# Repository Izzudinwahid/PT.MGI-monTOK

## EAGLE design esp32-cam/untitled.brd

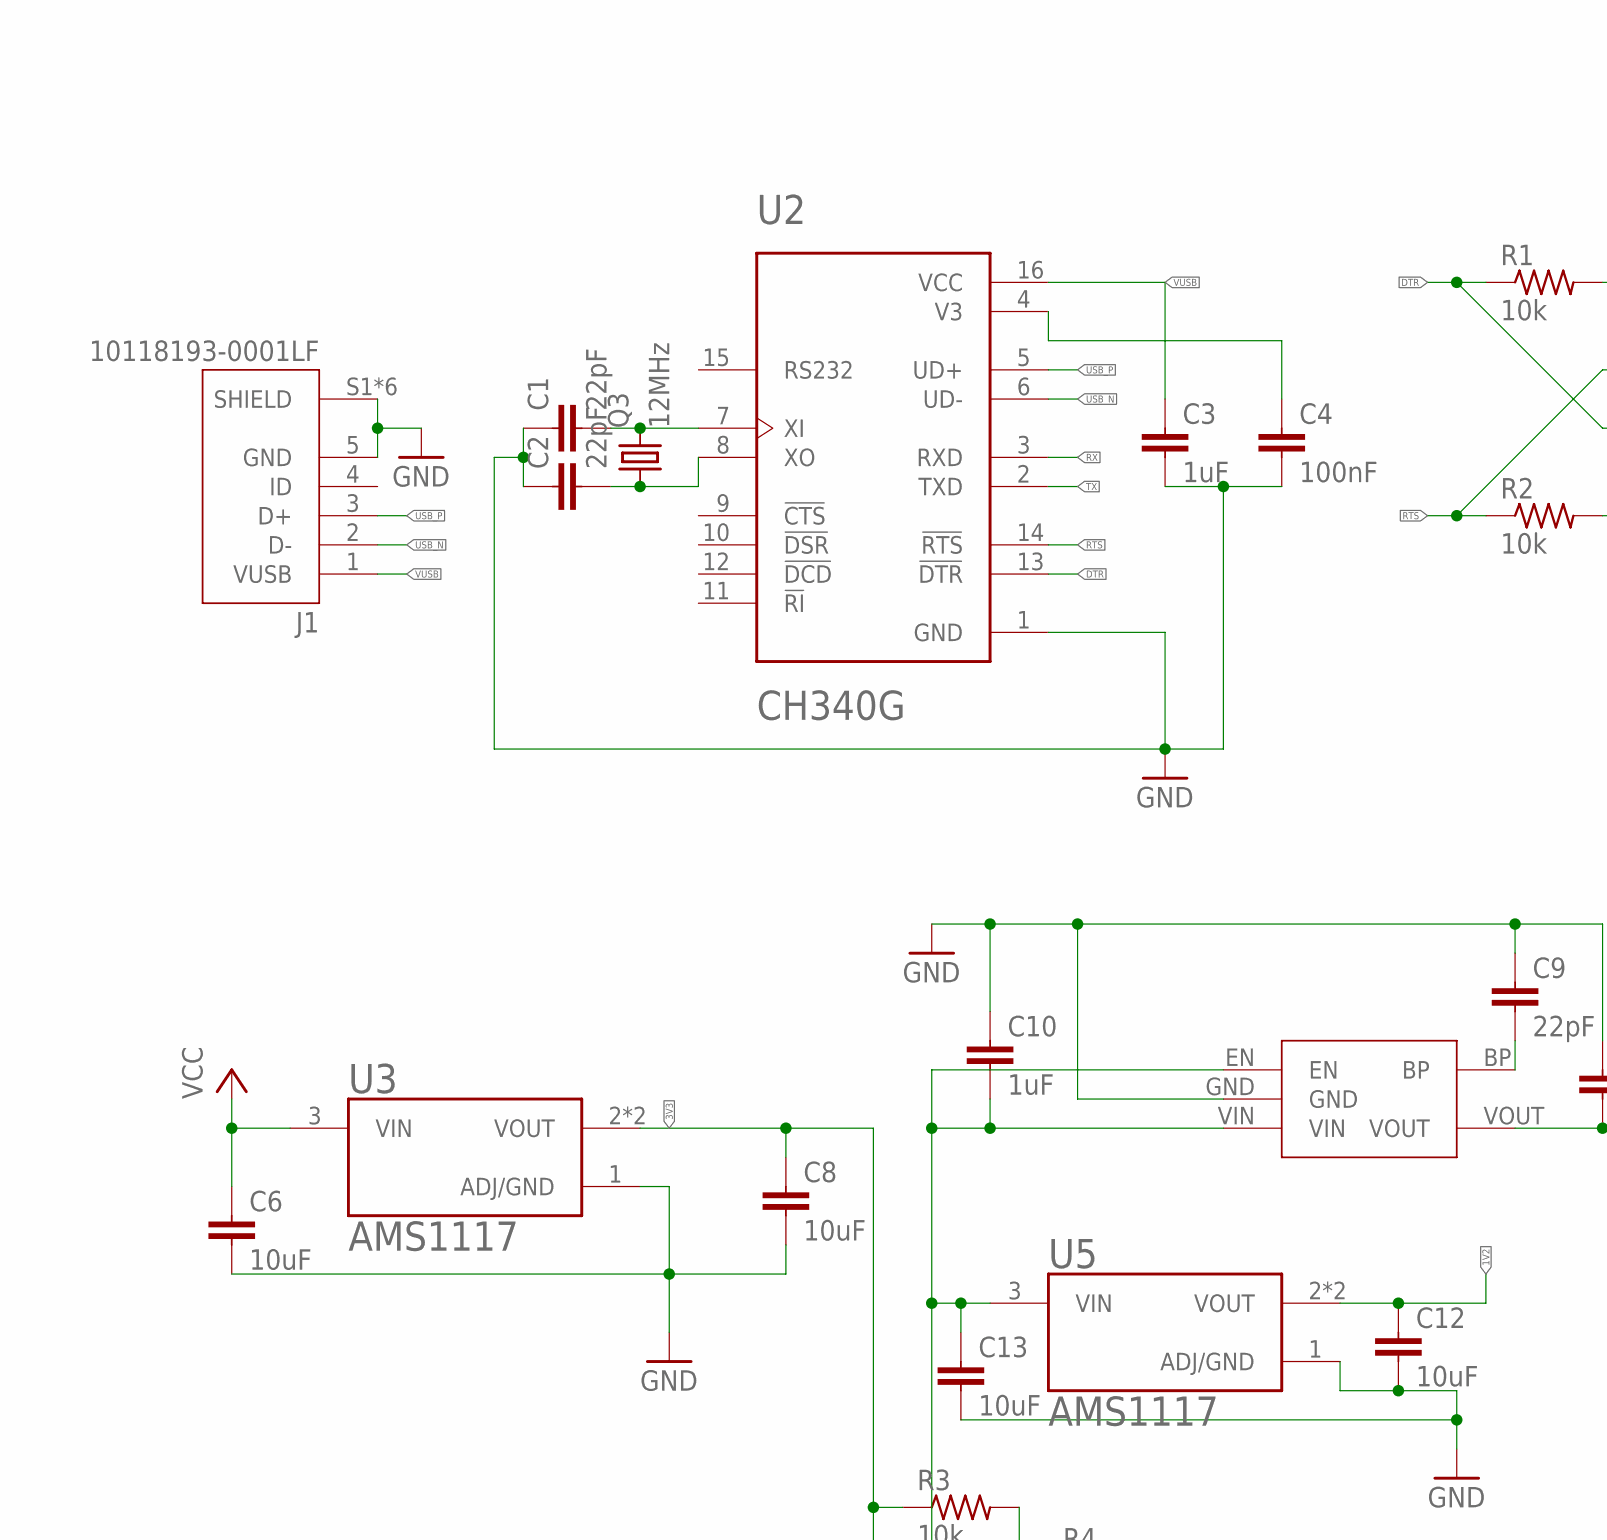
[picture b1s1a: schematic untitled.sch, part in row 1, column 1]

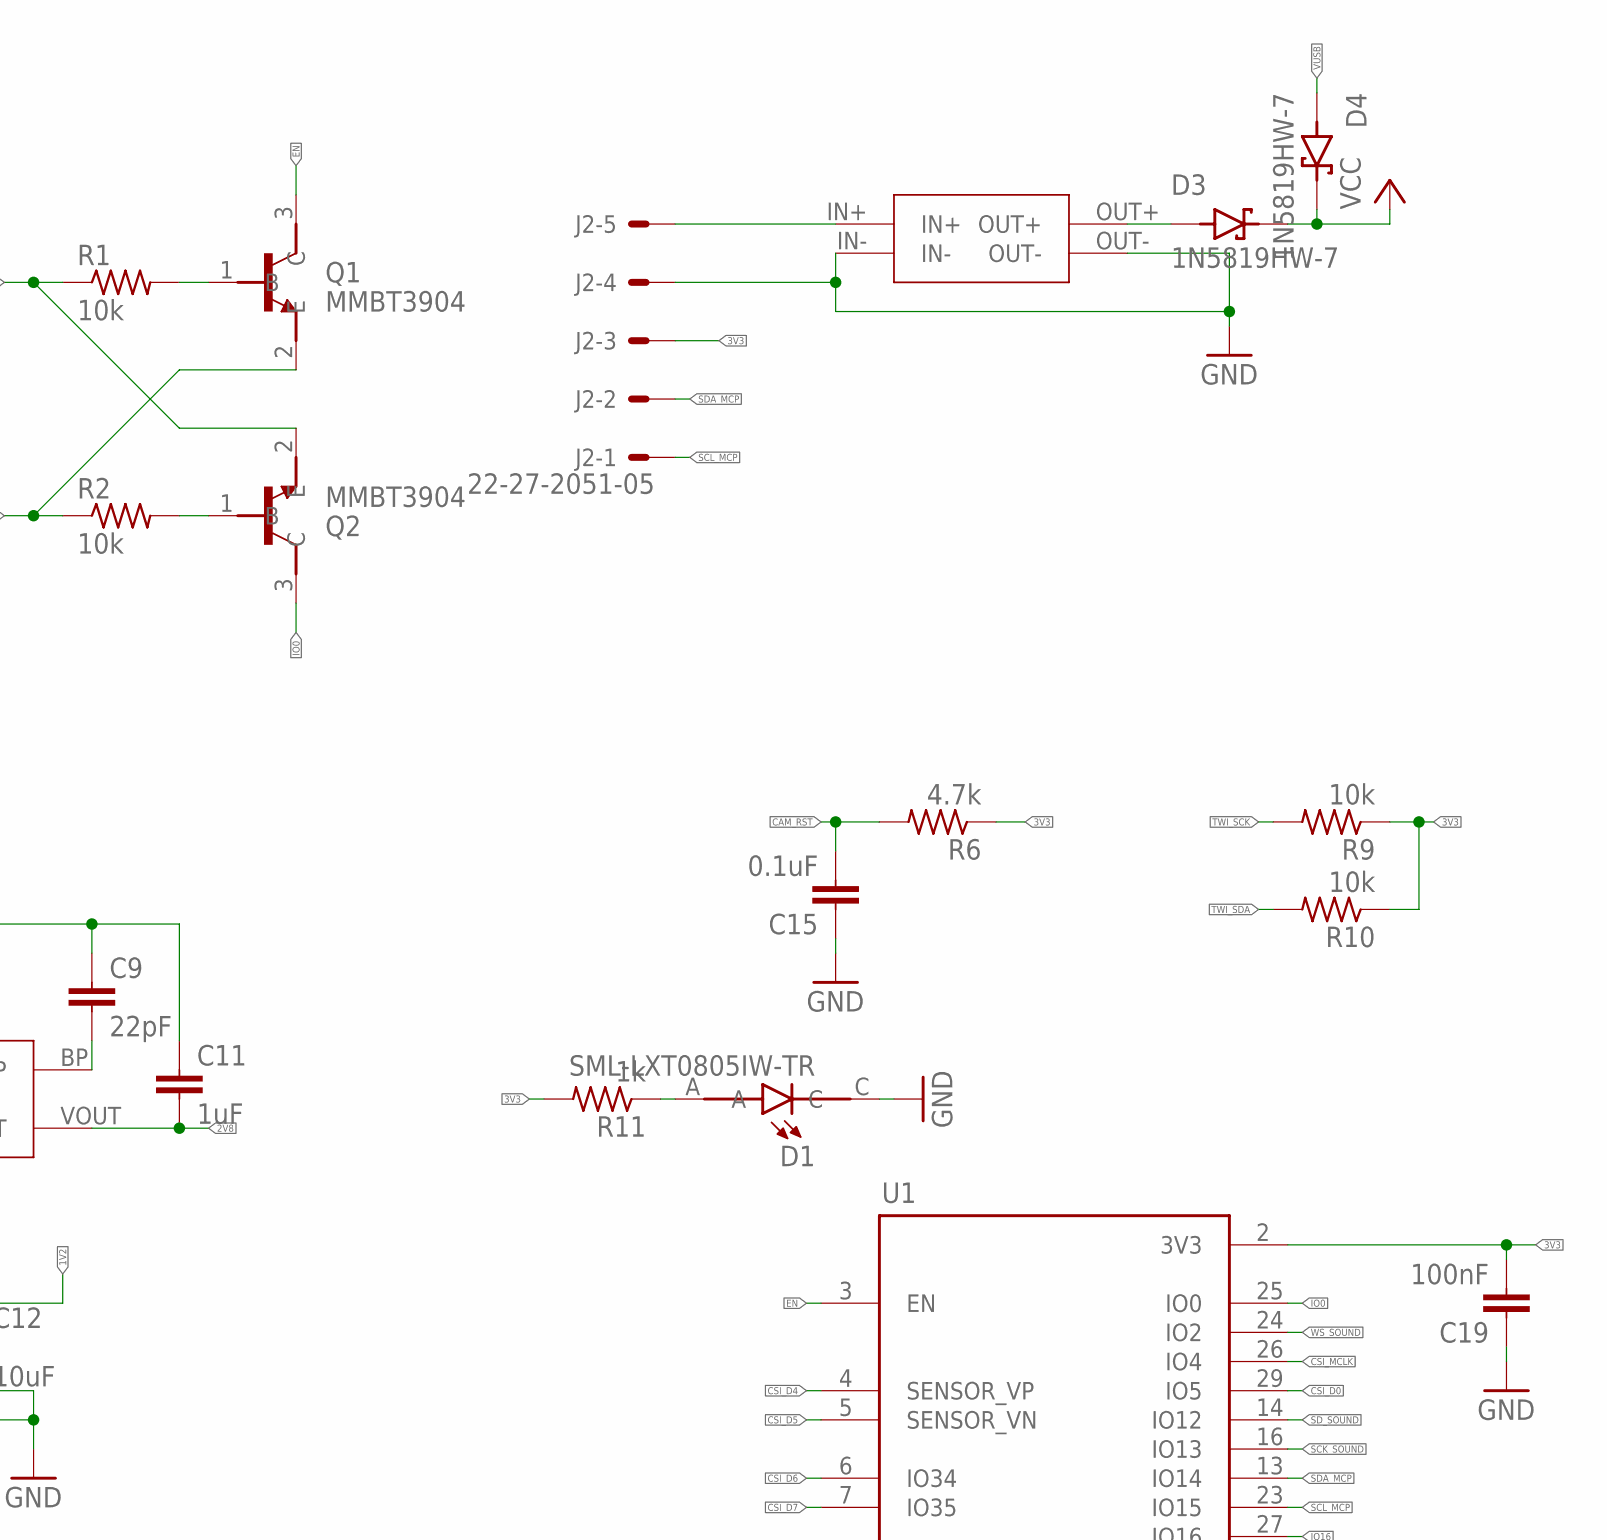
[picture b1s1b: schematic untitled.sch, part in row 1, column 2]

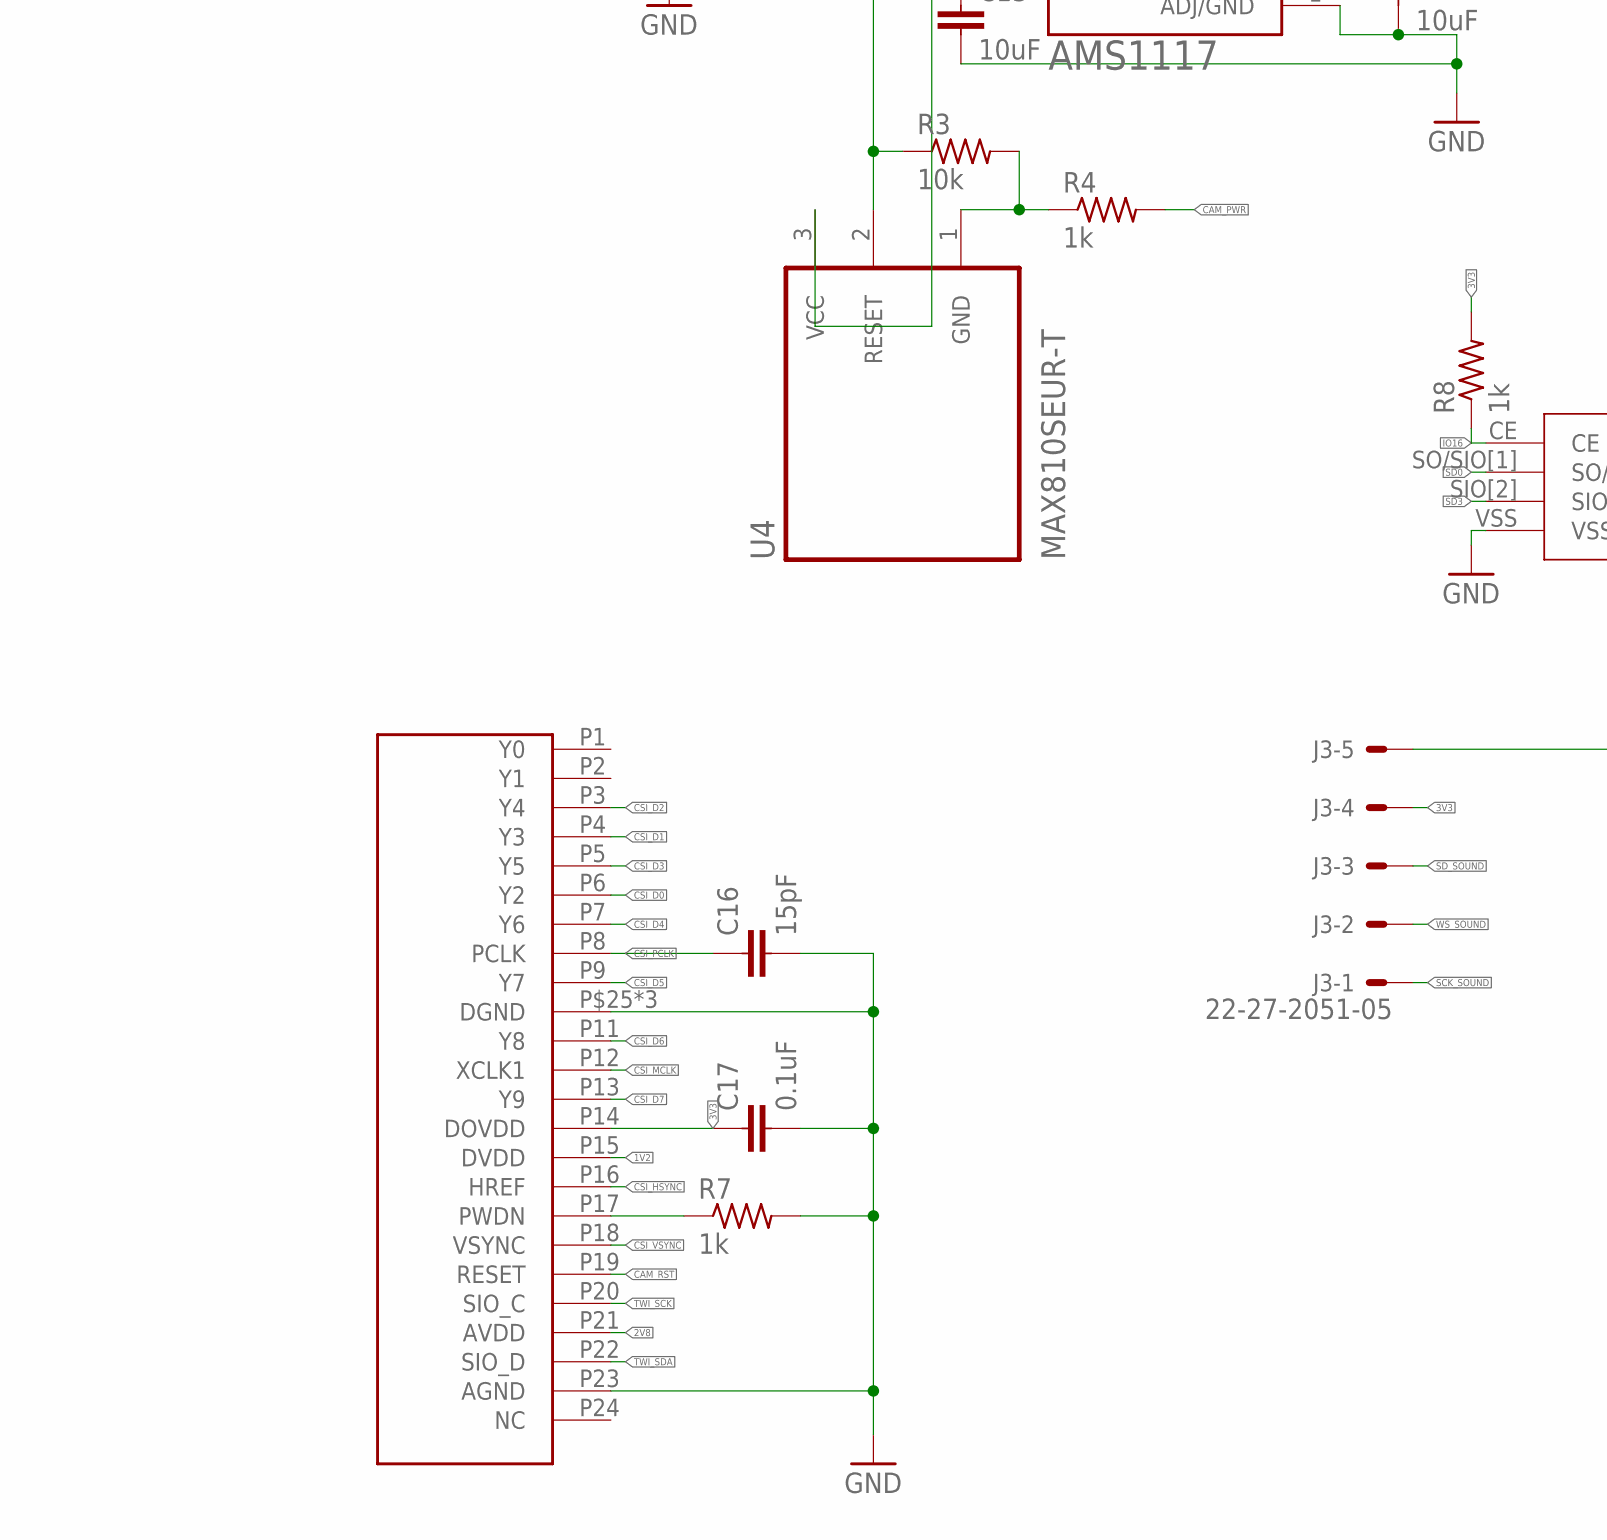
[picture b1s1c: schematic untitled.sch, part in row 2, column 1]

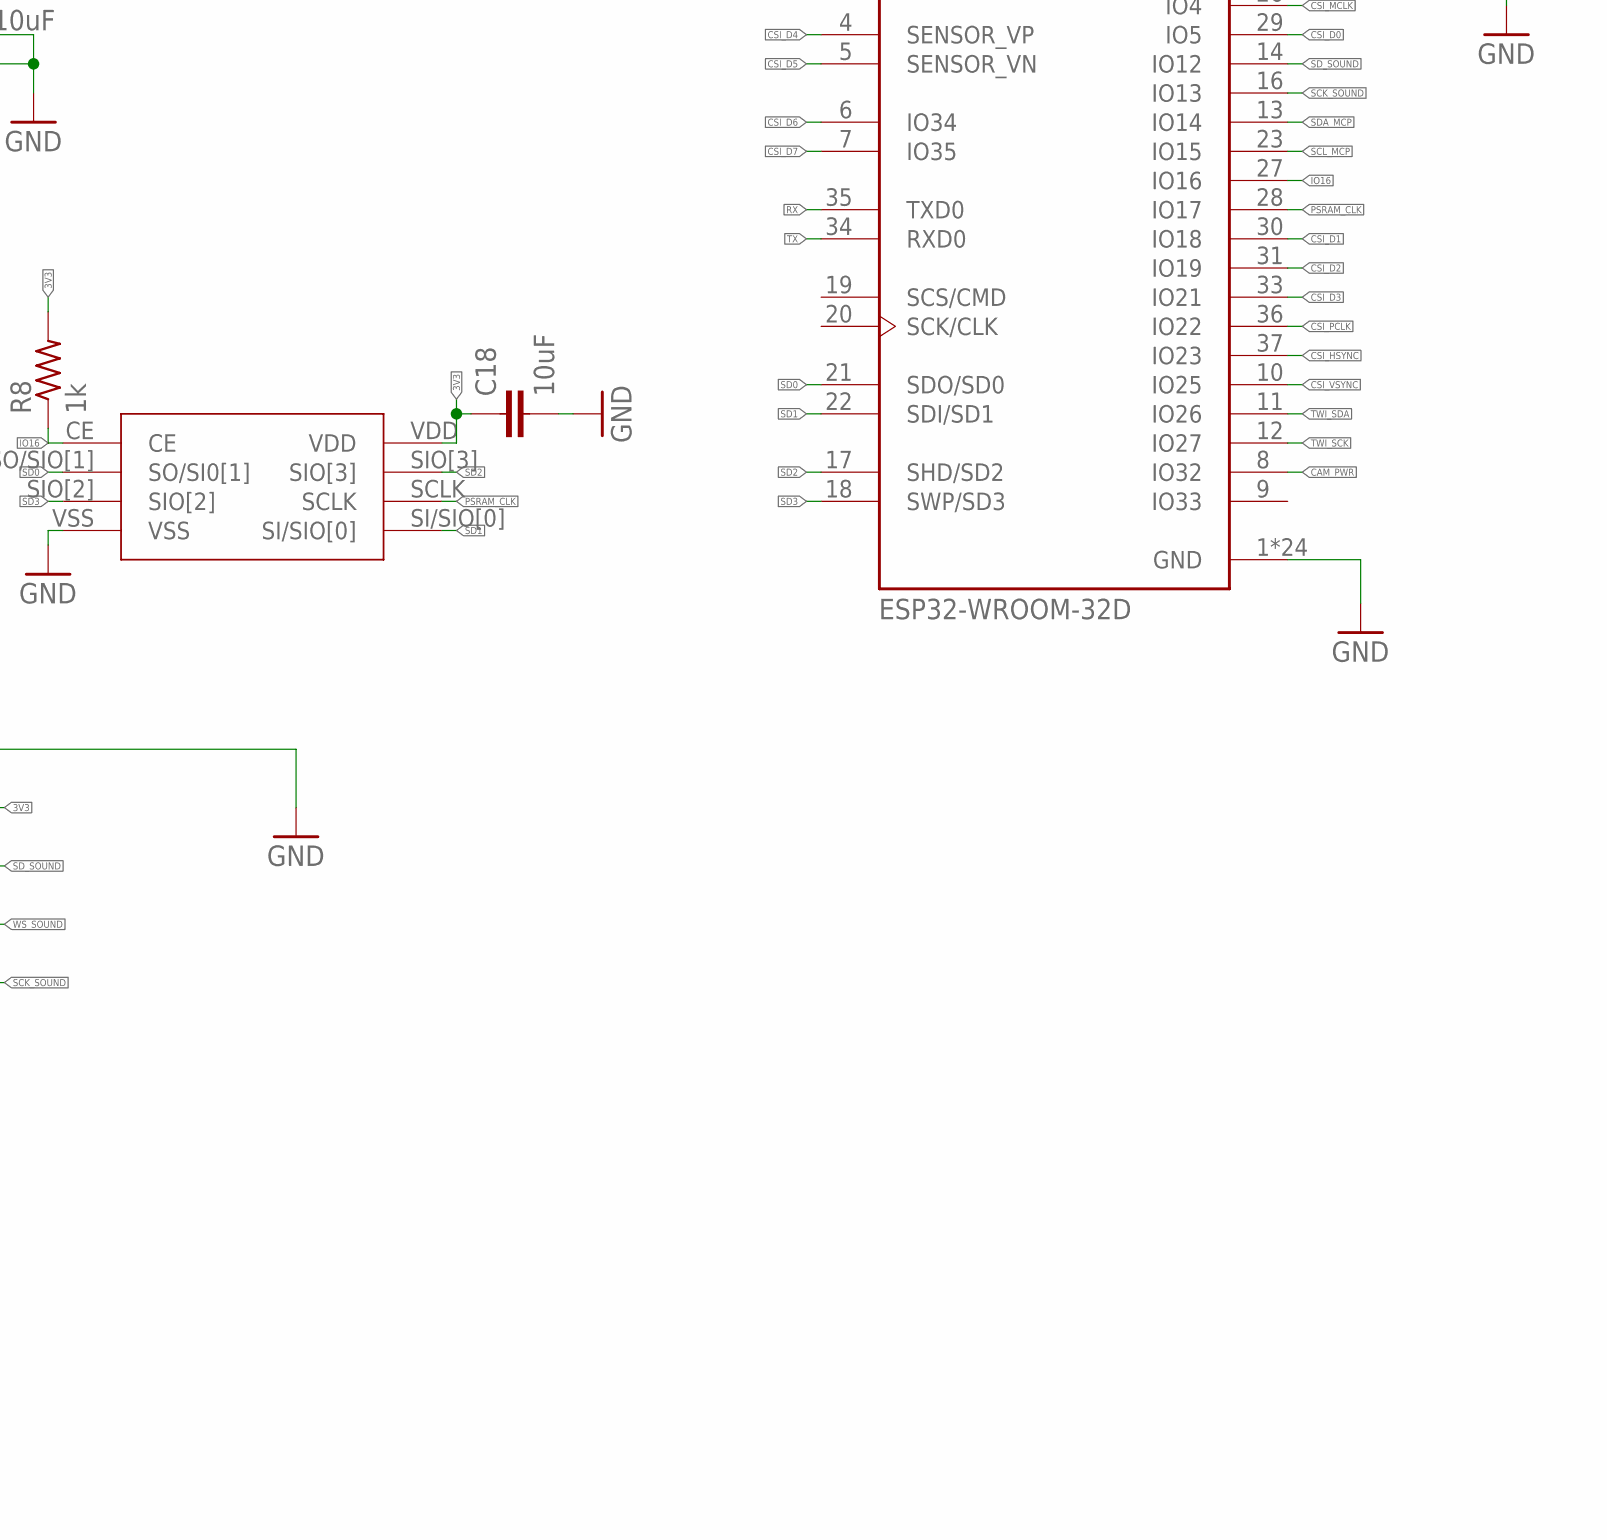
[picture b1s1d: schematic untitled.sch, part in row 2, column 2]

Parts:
APS6404L1: APS6404L
C1, C2, C9: 22pF; C0805K
C3, C10, C11: 1uF; C0805K
C4, C19: 100nF; C0805K
C6, C8, C12, C13, C18: 10uF; C0805K
C15, C17: 0.1uF; C0805K
C16: 15pF; C0805K
CAM1: OV2640; FPC-24
D1: SML-LXT0805IW-TR; LEDC2012X120N
D3, D4: 1N5819HW-7; SOD3715X145N
J1: 10118193-0001LF; FCI_10118193-0001LF
J2, J3: 22-27-2051-05; 6410-05
MINI1: MINI560
Q1, Q2: MMBT3904; SOT95P240X120-3N
Q3: 12MHz; SM49
R1, R2, R3, R9, R10: 10k; M0805
R4, R7, R8, R11: 1k; M0805
R6: 4.7k; M0805
RT9193-28GB1: RT9193-28GB; SOT94P279X129-5N
U1: ESP32-WROOM-32D; MODULE_ESP32-WROOM-32D
U2: CH340G; SOIC127P600X180-16N
U3, U5: AMS1117; SOT229P700X180-4N
U4: MAX810SEUR-T; SOT95P237X112-3N

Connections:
1V2: C12.1, CAM1.P15 (DVDD), U5.2 (VOUT), U5.4 (VOUT)
2V8: C11.2, CAM1.P21 (AVDD), RT9193-28GB1.VOUT
3V3: APS6404L1.VDD, C8.1, C17.1, C18.1, C19.2, CAM1.P14 (DOVDD), J2.3, J3.4, R3.1, R6.1, R8.2, R9.1, R10.1, R11.2, U1.2 (3V3), U3.2 (VOUT), U3.4 (VOUT), U4.2 (RESET)
CAM_PWR: R4.2, U1.8 (IO32)
CAM_RST: C15.2, CAM1.P19 (RESET), R6.2
CSI_D0: CAM1.P6 (Y2), U1.29 (IO5)
CSI_D1: CAM1.P4 (Y3), U1.30 (IO18)
CSI_D2: CAM1.P3 (Y4), U1.31 (IO19)
CSI_D3: CAM1.P5 (Y5), U1.33 (IO21)
CSI_D4: CAM1.P7 (Y6), U1.4 (SENSOR_VP)
CSI_D5: CAM1.P9 (Y7), U1.5 (SENSOR_VN)
CSI_D6: CAM1.P11 (Y8), U1.6 (IO34)
CSI_D7: CAM1.P13 (Y9), U1.7 (IO35)
CSI_HSYNC: CAM1.P16 (HREF), U1.37 (IO23)
CSI_MCLK: CAM1.P12 (XCLK1), U1.26 (IO4)
CSI_PCLK: C16.1, CAM1.P8 (PCLK), U1.36 (IO22)
CSI_VSYNC: CAM1.P18 (VSYNC), U1.10 (IO25)
DTR: Q2.2 (E), R1.1, U2.13 (!DTR)
EN: Q1.3 (C), U1.3 (EN)
GND: APS6404L1.VSS, C1.1, C2.1, C3.2, C4.2, C6.2, C8.2, C9.1, C10.1, C11.1, C12.2, C13.2, C15.1, C16.2, C17.2, C18.2, C19.1, CAM1.P10 (DGND), CAM1.P23 (AGND), CAM1.P$25 (DGND), CAM1.P$26 (DGND), D1.C, J1.5 (GND), J1.S1 (SHIELD), J1.S2 (SHIELD), J1.S3 (SHIELD), J1.S4 (SHIELD), J1.S5 (SHIELD), J1.S6 (SHIELD), J2.4, J3.5, MINI1.IN-, MINI1.OUT-, R7.2, RT9193-28GB1.GND, U1.1 (GND), U1.15 (GND), U1.38 (GND), U1.39_1 (GND), U1.39_2 (GND), U1.39_3 (GND), U1.39_4 (GND), U1.39_5 (GND), U1.39_6 (GND), U1.39_7 (GND), U1.39_8 (GND), U1.39_9 (GND), U1.39_10 (GND), U1.39_11 (GND), U1.39_12 (GND), U1.39_13 (GND), U1.39_14 (GND), U1.39_15 (GND), U1.39_16 (GND), U1.39_17 (GND), U1.39_18 (GND), U1.39_19 (GND), U1.39_20 (GND), U1.39_21 (GND), U2.1 (GND), U3.1 (ADJ/GND), U5.1 (ADJ/GND)
IO0: Q2.3 (C), U1.25 (IO0)
IO16: APS6404L1.CE, R8.1, U1.27 (IO16)
unnamed: C1.2, Q3.2, U2.7 (XI)
unnamed: C2.2, Q3.1, U2.8 (XO)
unnamed: Q1.1 (B), R1.2
unnamed: R3.2, R4.1, U4.1 (GND)
unnamed: D1.A, R11.1
unnamed: J2.5, MINI1.IN+
unnamed: C10.2, C13.1, RT9193-28GB1.EN, RT9193-28GB1.VIN, U4.3 (VCC), U5.3 (VIN)
unnamed: C4.1, U2.4 (V3)
unnamed: Q2.1 (B), R2.2
unnamed: C9.2, RT9193-28GB1.BP
unnamed: D3.A, MINI1.OUT+
unnamed: CAM1.P17 (PWDN), R7.1
PSRAM_CLK: APS6404L1.SCLK, U1.28 (IO17)
RTS: Q1.2 (E), R2.1, U2.14 (!RTS)
RX: U1.35 (TXD0), U2.3 (RXD)
SCK_SOUND: J3.1, U1.16 (IO13)
SCL_MCP: J2.1, U1.23 (IO15)
SD0: APS6404L1.SO/SIO[1] (SO/SI0[1]), U1.21 (SDO/SD0)
SD1: APS6404L1.SI/SIO[0], U1.22 (SDI/SD1)
SD2: APS6404L1.SIO[3], U1.17 (SHD/SD2)
SD3: APS6404L1.SIO[2], U1.18 (SWP/SD3)
SDA_MCP: J2.2, U1.13 (IO14)
SD_SOUND: J3.3, U1.14 (IO12)
TWI_SCK: CAM1.P20 (SIO_C), R9.2, U1.12 (IO27)
TWI_SDA: CAM1.P22 (SIO_D), R10.2, U1.11 (IO26)
TX: U1.34 (RXD0), U2.2 (TXD)
USB_N: J1.2 (D-), U2.6 (UD-)
USB_P: J1.3 (D+), U2.5 (UD+)
VCC: C6.1, D3.C (K), D4.C (K), U3.3 (VIN)
VUSB: C3.1, D4.A, J1.1 (VUSB), U2.16 (VCC)
WS_SOUND: J3.2, U1.24 (IO2)

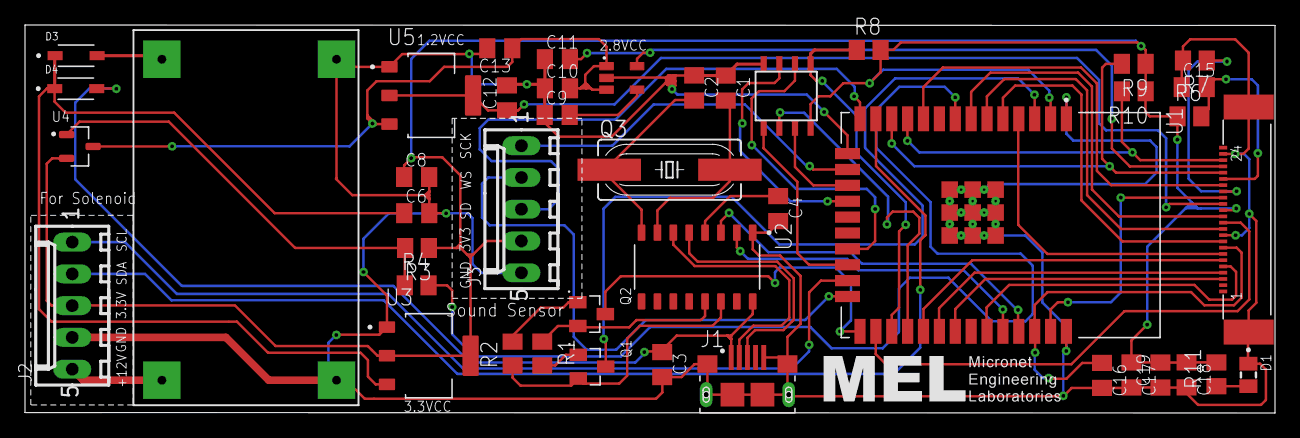
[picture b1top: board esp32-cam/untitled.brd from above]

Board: 2 copper layers, 100.0 x 31.0 mm, 44 parts (0 on the bottom side), 53 nets.

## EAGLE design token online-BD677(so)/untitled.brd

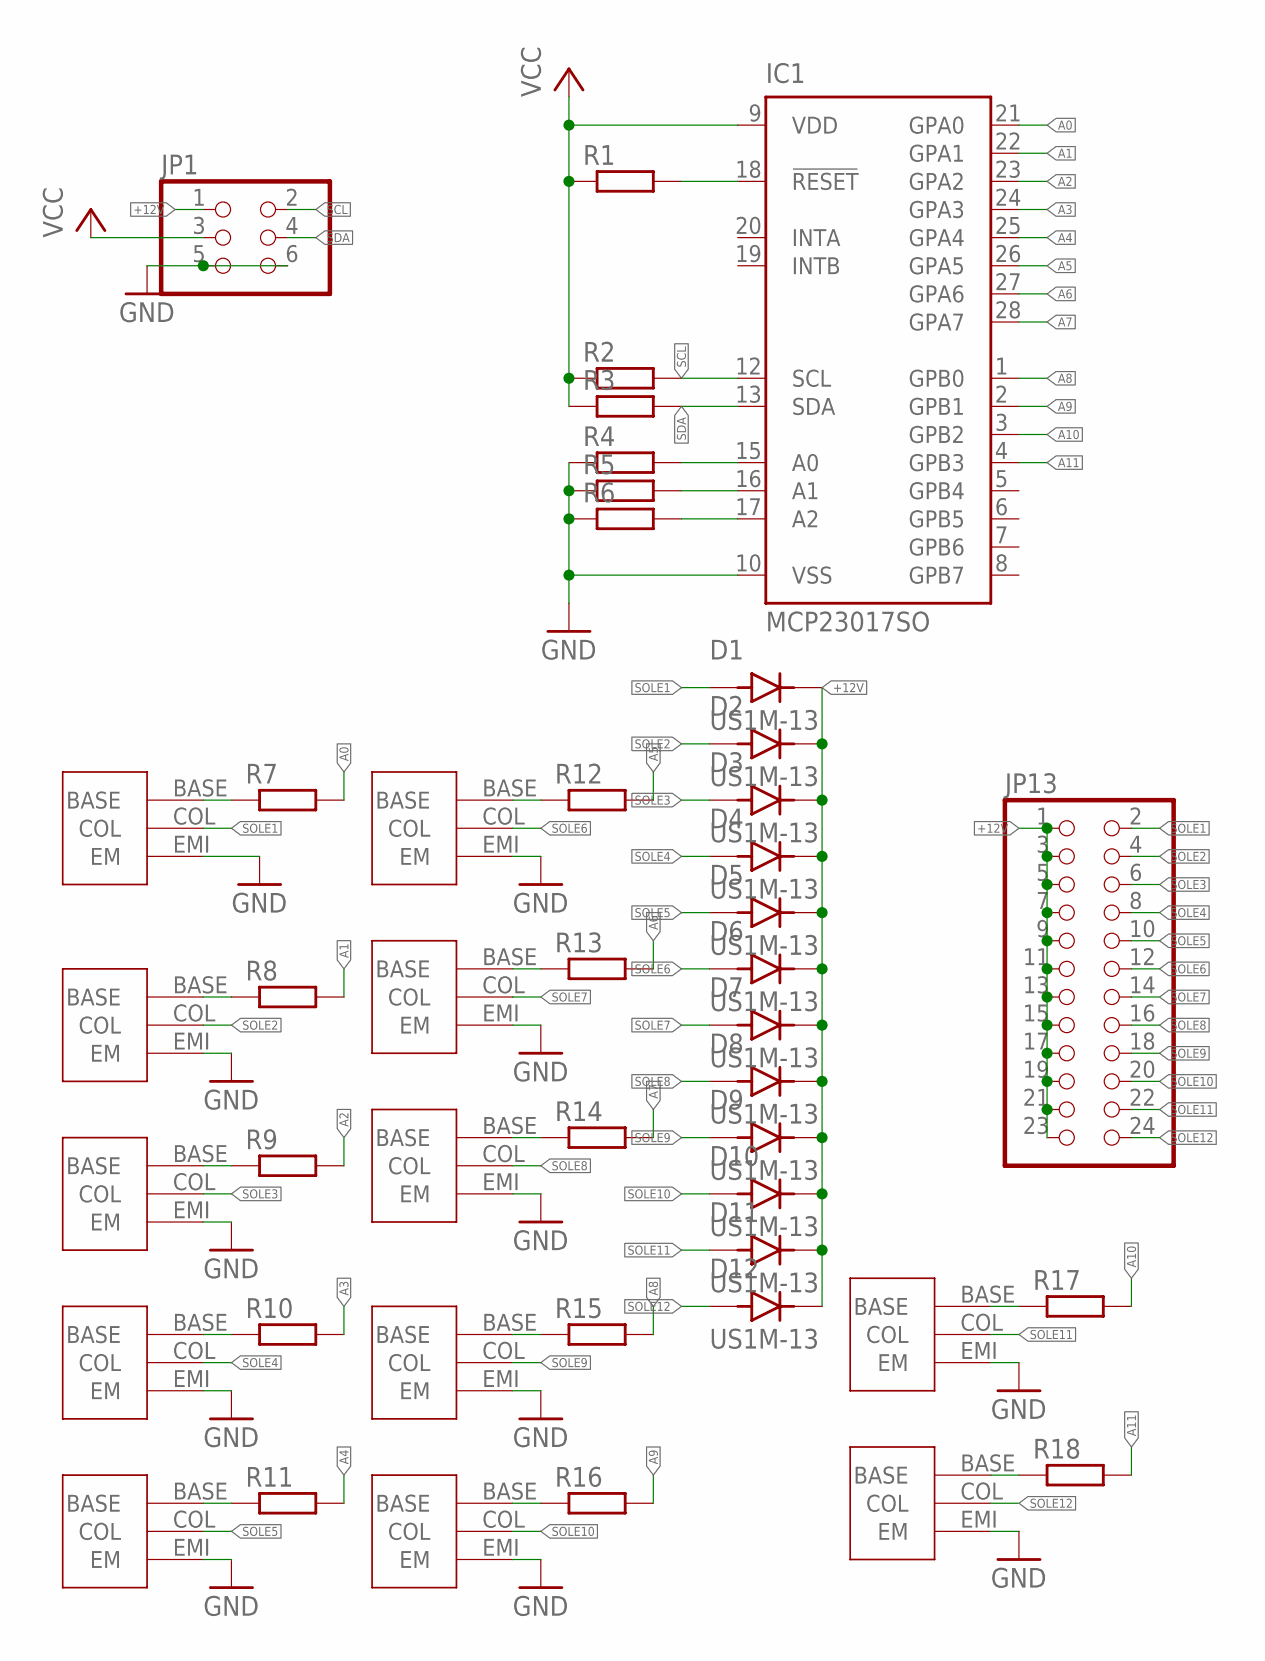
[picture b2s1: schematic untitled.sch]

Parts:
BD677-SMD1, BD677-SMD2, BD677-SMD3, BD677-SMD4, BD677-SMD5, BD677-SMD6, BD677-SMD7, BD677-SMD8, BD677-SMD9, BD677-SMD10, BD677-SMD11, BD677-SMD12: BD677-SMD
D1, D2, D3, D4, D5, D6, D7, D8, D9, D10, D11, D12: US1M-13; DIOM5226X240N
IC1: MCP23017SO; SO28W
JP1: PINHD-2X3; 2X03
JP13: PINHD-2X12; 2X12
R1, R2, R3, R4, R5, R6, R7, R8, R9, R10, R11, R12, R13, R14, R15, R16, R17, R18: R-EU_R0805; R0805

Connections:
+12V: D1.C (K), D2.C (K), D3.C (K), D4.C (K), D5.C (K), D6.C (K), D7.C (K), D8.C (K), D9.C (K), D10.C (K), D11.C (K), D12.C (K), JP1.1, JP13.1, JP13.3, JP13.5, JP13.7, JP13.9, JP13.11, JP13.13, JP13.15, JP13.17, JP13.19, JP13.21, JP13.23
A0: IC1.21 (GPA0), R7.2
A1: IC1.22 (GPA1), R8.2
A2: IC1.23 (GPA2), R9.2
A3: IC1.24 (GPA3), R10.2
A4: IC1.25 (GPA4), R11.2
A5: IC1.26 (GPA5), R12.2
A6: IC1.27 (GPA6), R13.2
A7: IC1.28 (GPA7), R14.2
A8: IC1.1 (GPB0), R15.2
A9: IC1.2 (GPB1), R16.2
A10: IC1.3 (GPB2), R17.2
A11: IC1.4 (GPB3), R18.2
GND: BD677-SMD1.EMI (EM), BD677-SMD2.EMI (EM), BD677-SMD3.EMI (EM), BD677-SMD4.EMI (EM), BD677-SMD5.EMI (EM), BD677-SMD6.EMI (EM), BD677-SMD7.EMI (EM), BD677-SMD8.EMI (EM), BD677-SMD9.EMI (EM), BD677-SMD10.EMI (EM), BD677-SMD11.EMI (EM), BD677-SMD12.EMI (EM), IC1.10 (VSS), JP1.5, JP1.6, R4.1, R5.1, R6.1
unnamed: IC1.18 (!RESET), R1.2
unnamed: BD677-SMD1.BASE, R7.1
unnamed: BD677-SMD2.BASE, R8.1
unnamed: IC1.15 (A0), R4.2
unnamed: IC1.16 (A1), R5.2
unnamed: IC1.17 (A2), R6.2
unnamed: BD677-SMD3.BASE, R9.1
unnamed: BD677-SMD6.BASE, R12.1
unnamed: BD677-SMD7.BASE, R13.1
unnamed: BD677-SMD8.BASE, R14.1
unnamed: BD677-SMD4.BASE, R10.1
unnamed: BD677-SMD5.BASE, R11.1
unnamed: BD677-SMD9.BASE, R15.1
unnamed: BD677-SMD10.BASE, R16.1
unnamed: BD677-SMD11.BASE, R17.1
unnamed: BD677-SMD12.BASE, R18.1
SCL: IC1.12 (SCL), JP1.2, R2.2
SDA: IC1.13 (SDA), JP1.4, R3.2
SOLE1: BD677-SMD1.COL, D1.A, JP13.2
SOLE2: BD677-SMD2.COL, D2.A, JP13.4
SOLE3: BD677-SMD3.COL, D3.A, JP13.6
SOLE4: BD677-SMD4.COL, D4.A, JP13.8
SOLE5: BD677-SMD5.COL, D5.A, JP13.10
SOLE6: BD677-SMD6.COL, D6.A, JP13.12
SOLE7: BD677-SMD7.COL, D7.A, JP13.14
SOLE8: BD677-SMD8.COL, D8.A, JP13.16
SOLE9: BD677-SMD9.COL, D9.A, JP13.18
SOLE10: BD677-SMD10.COL, D10.A, JP13.20
SOLE11: BD677-SMD11.COL, D11.A, JP13.22
SOLE12: BD677-SMD12.COL, D12.A, JP13.24
VCC: IC1.9 (VDD), JP1.3, R1.1, R2.1, R3.1

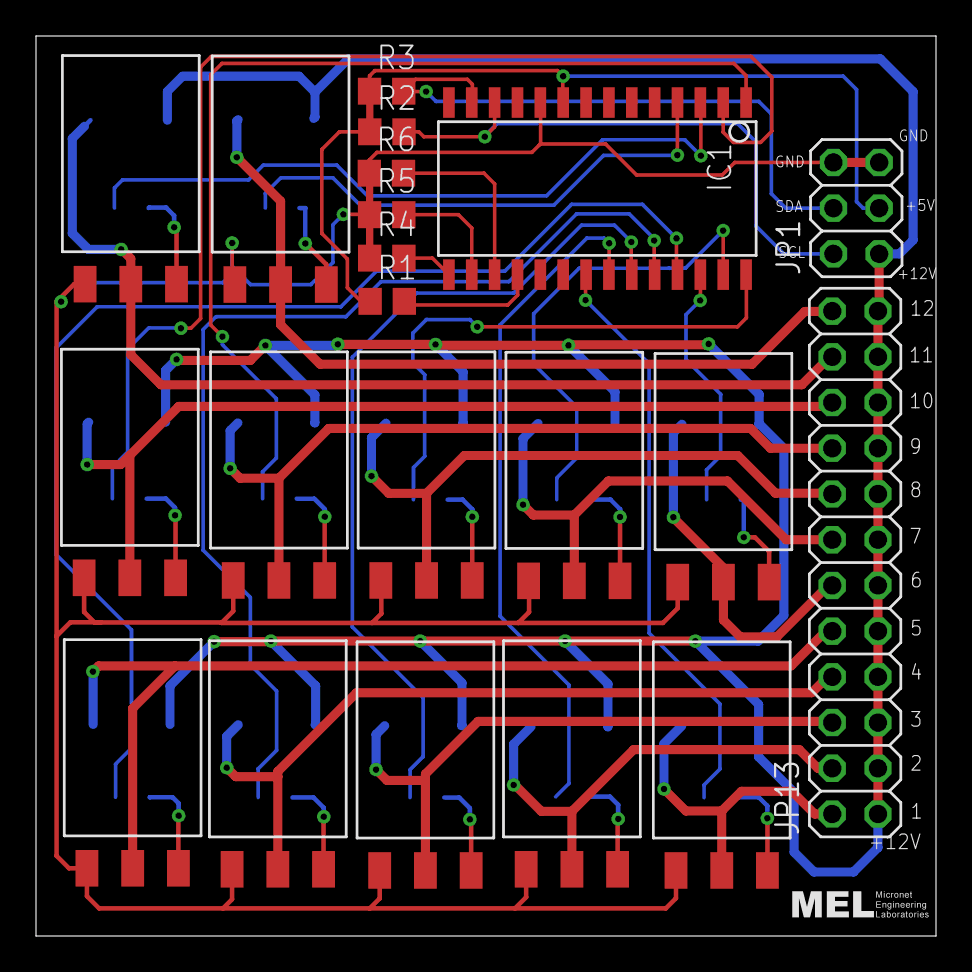
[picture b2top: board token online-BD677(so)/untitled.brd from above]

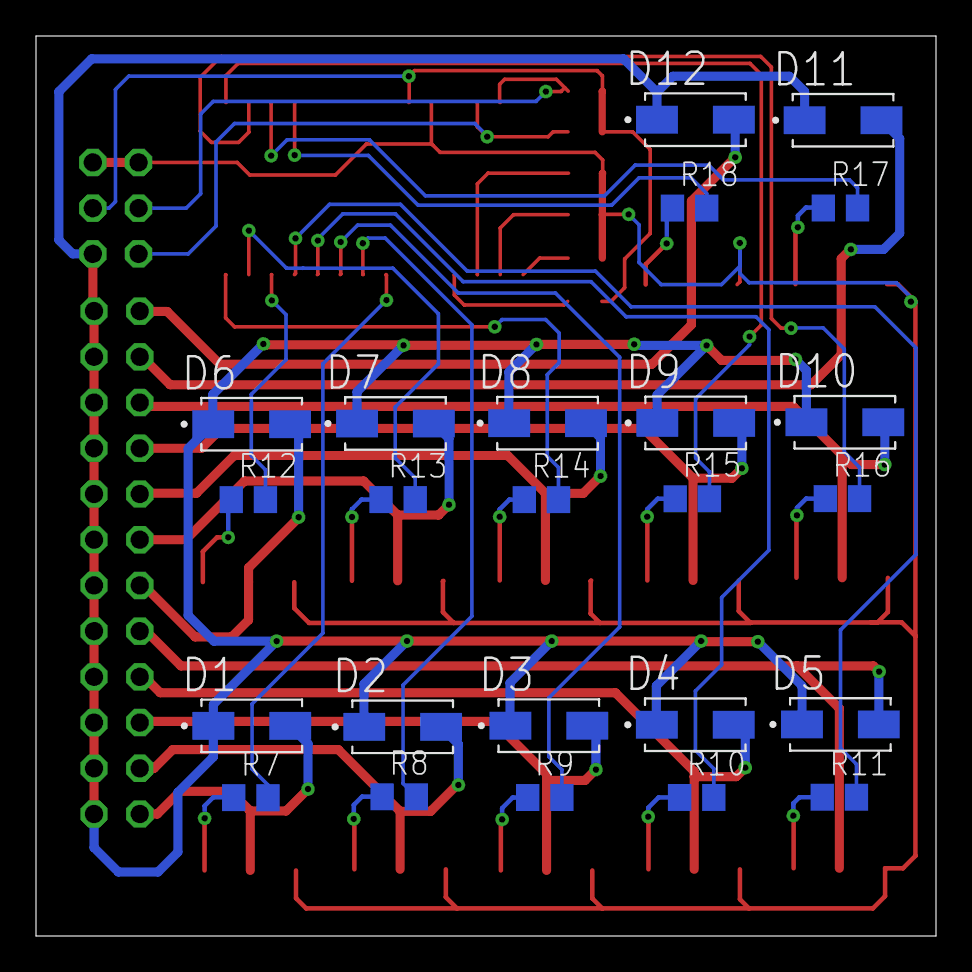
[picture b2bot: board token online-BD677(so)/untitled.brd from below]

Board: 2 copper layers, 50.0 x 50.0 mm, 45 parts (24 on the bottom side), 45 nets.

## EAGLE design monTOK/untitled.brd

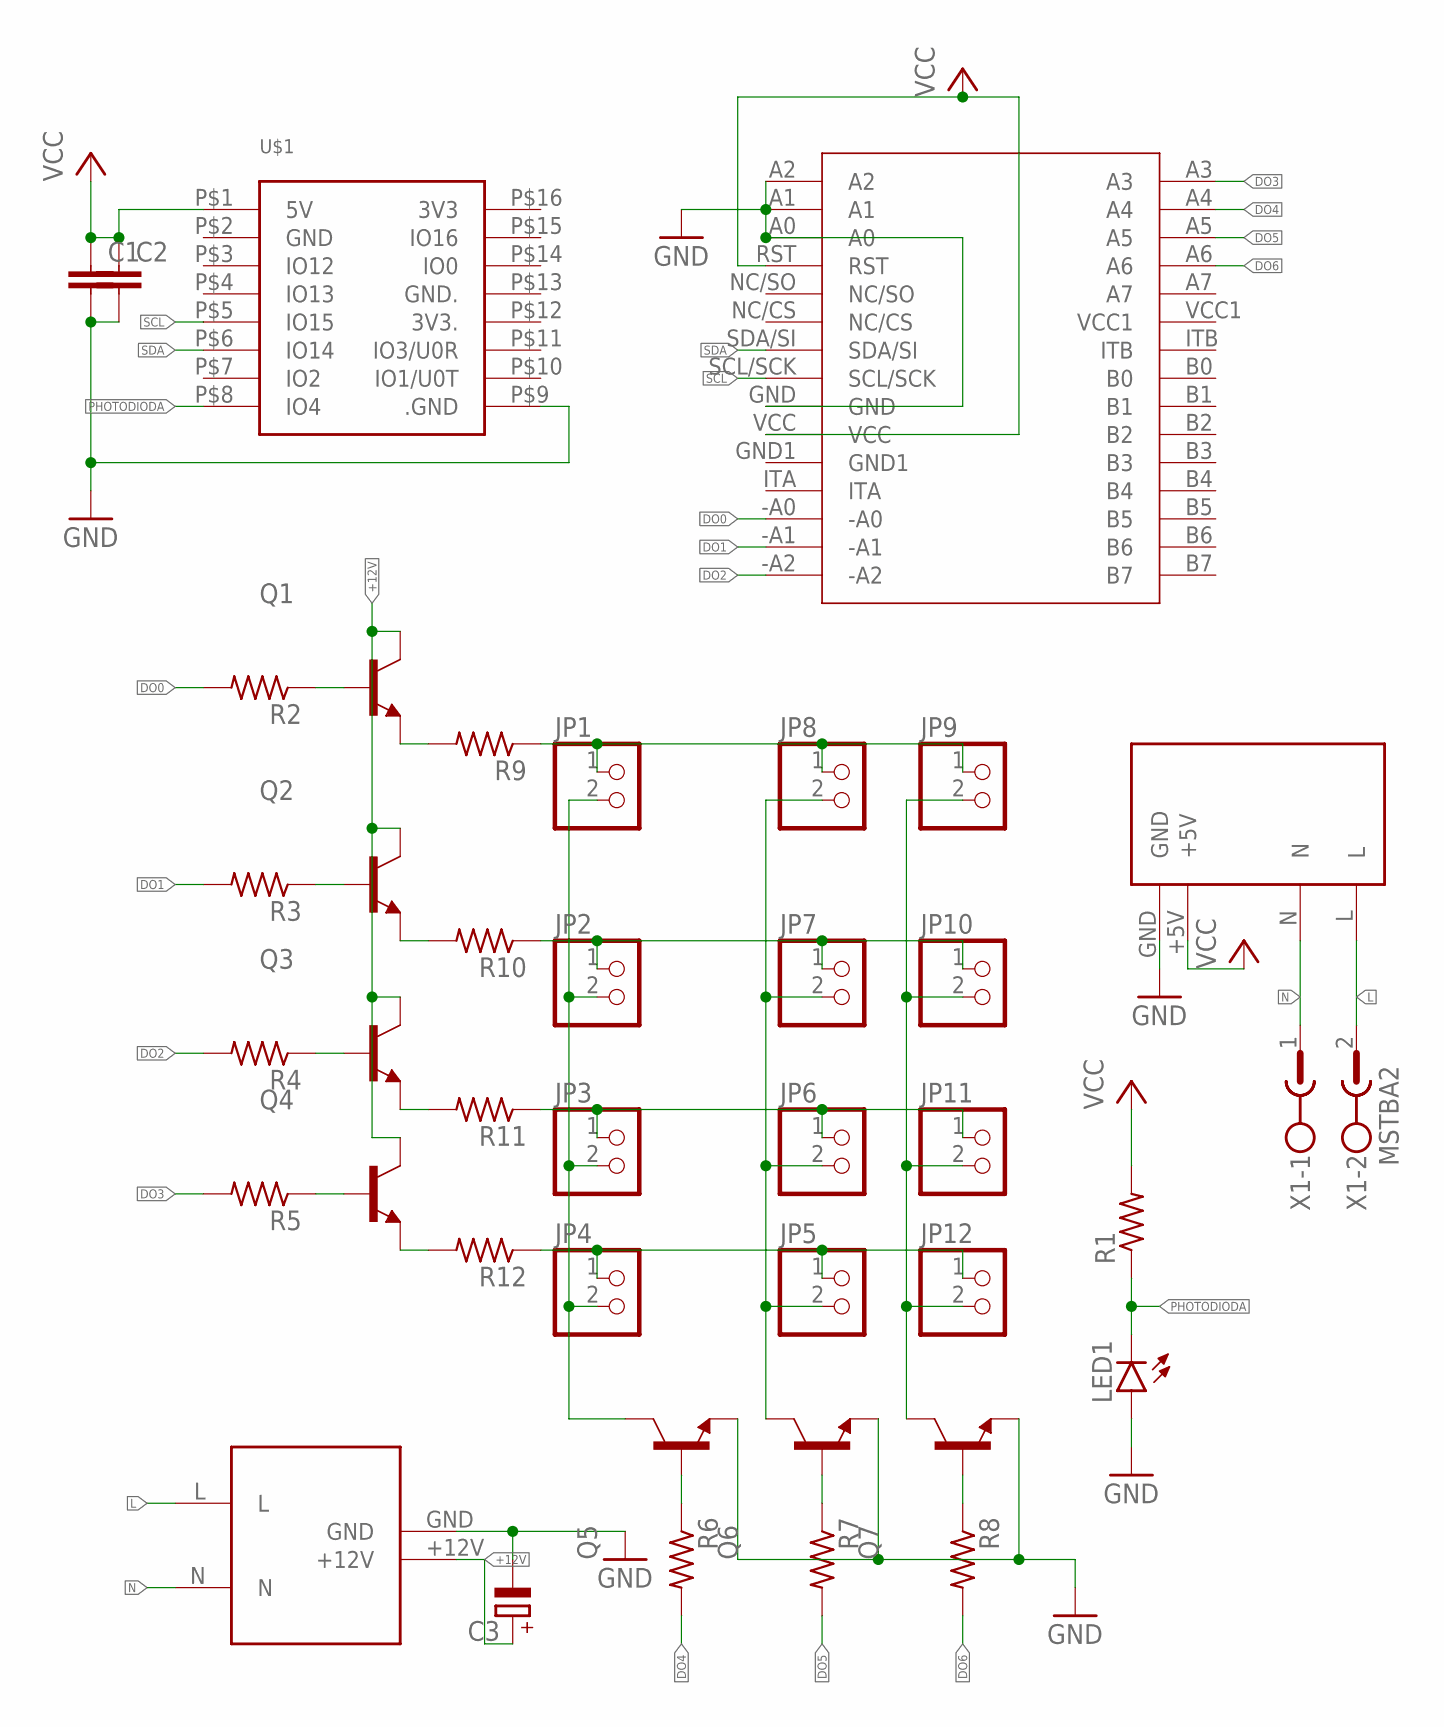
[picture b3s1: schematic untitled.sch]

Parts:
C1, C2: C-EUC0805K; C0805K
C3: CPOL-EU153CLV-0505; 153CLV-0505
HLK-15M1: HLK-15M12
JP1, JP2, JP3, JP4, JP5, JP6, JP7, JP8, JP9, JP10, JP11, JP12: PINHD-1X2; 1X02
LED1: LED5MM
MCP1: MCP23017
Q1, Q2, Q3, Q4, Q5, Q6, Q7: BCW31SMD; SOT23-BEC
R1, R2, R3, R4, R5, R6, R7, R8, R9, R10, R11, R12: R-US_M0805; M0805
U$1: ESP32-CAM
WX-DC1: WX-DC12003
X1: MSTBA2

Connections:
+12V: C3.+, HLK-15M1.+12V, Q1.C, Q2.C, Q3.C, Q4.C
DO0: MCP1.-A0, R2.2
DO1: MCP1.-A1, R3.2
DO2: MCP1.-A2, R4.2
DO3: MCP1.A3, R5.2
DO4: MCP1.A4, R6.2
DO5: MCP1.A5, R7.2
DO6: MCP1.A6, R8.2
GND: C1.2, C2.2, C3.-, HLK-15M1.GND, LED1.A, MCP1.A0, MCP1.A1, MCP1.A2, MCP1.GND, Q5.E, Q6.E, Q7.E, U$1.P$9 (.GND), WX-DC1.GND
L: HLK-15M1.L, WX-DC1.L, X1.2
N: HLK-15M1.N, WX-DC1.N, X1.1
unnamed: Q1.B, R2.1
unnamed: Q2.B, R3.1
unnamed: Q3.B, R4.1
unnamed: Q4.B, R5.1
unnamed: JP1.2, JP2.2, JP3.2, JP4.2, Q5.C
unnamed: Q5.B, R6.1
unnamed: Q6.B, R7.1
unnamed: Q7.B, R8.1
unnamed: Q1.E, R9.2
unnamed: Q2.E, R10.2
unnamed: Q3.E, R11.2
unnamed: Q4.E, R12.2
unnamed: JP1.1, JP8.1, JP9.1, R9.1
unnamed: JP2.1, JP7.1, JP10.1, R10.1
unnamed: JP3.1, JP6.1, JP11.1, R11.1
unnamed: JP4.1, JP5.1, JP12.1, R12.1
unnamed: JP5.2, JP6.2, JP7.2, JP8.2, Q6.C
unnamed: JP9.2, JP10.2, JP11.2, JP12.2, Q7.C
PHOTODIODA: LED1.K (C), R1.1, U$1.P$8 (IO4)
SCL: MCP1.SCL/SCK, U$1.P$5 (IO15)
SDA: MCP1.SDA/SI, U$1.P$6 (IO14)
VCC: C1.1, C2.1, MCP1.RST, MCP1.VCC, R1.2, U$1.P$1 (5V), WX-DC1.+5V

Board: 2 copper layers, 40 parts (0 on the bottom side), 33 nets, no tracks yet.

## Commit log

2022-11-01 pcb monTOK
2022-11-25 revisi PCB
2022-11-25 menghapus desain pertama
2022-11-25 menambahkan label
2022-12-07 menggunakan transistor BD677
2023-01-11 perubahan desain MSP23017-so
2023-02-08 revisi tanggal 08/02/2023(desain ESPCAM)
